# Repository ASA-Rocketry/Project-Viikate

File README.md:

# Project Viikate

## Getting started

```bash
git clone https://github.com/ASA-Rocketry/Project-Viikate
cd Project-Viikate
./setup.sh --wizard --build
```

Run `./setup.sh --help` for options, or see the [codebase setup guide](docs/codebase-setup.md) for prerequisites, manual setup, and flashing instructions.

## Structure

```
project-viikate/
  cad/          -- the fusion files for the structure of the rocket
  code/         -- firmware, simulations and other adjacent software
    firmware/   -- the actual firmware that goes on the rocket
    dashboard/
  docs/         -- textual documentation related to the operations of the project
  minutes/      -- meeting notes
  pcb/          -- electronics, pinouts and the core PCB
```

## Software

## Style Choices

- For details on how to style your code refer to [RocketStyle](./code/README.md).
- For details on how to style your mechanical designs refer to [Mechanical Design Guide for Aalto Space Association Projects with Fusion](./cad/README.md).
- Folder names should follow `kebab-case` unless mandated by the style guide of the specific piece of software.
- Files should follow `snake_case` unless mandated by the style guide of a specific piece of software.

## Testing Policy

The priority of tests is strictly in this order:

0. Structural failures.
1. Serialization/deserialization.
2. Unit conversions.
3. Sensor fusion edgecases.
4. State machine transitions.
5. Numerical stability.
6. Watchdog/fault recovery.

Notice how getters and setters are not included. They are not important.

## How to make Git less painful

- Use rebases instead of merges. Merges pollute history, rebases straighten it back out.
- Don't commit stuff that is not supposed to be `diff`-ed. If you can't meaningfully interpret a file changing across time it should not be in git.
- Don't commit caches. Temporary files, output binaries, stuff like that.
- A commit message should follow the strict `type(scope): Message` format. This is needed to make the scope of the changes easier to understand. For example: `feat(gnc): Add the barrel roll logic`. The accepted types are as follows:
  - `feat` - a new feature, functionality that was previously missing.
  - `fix` - a fix to a bug that was causing trouble.
  - `style` - making some part of the code adhere to a style.
  - `docs` - adding documentation, amending typos.
  - `refactor` - making an old piece of code less ugly.
  - `chore` - reordering files, deleting stuff that shouldn't be tracked, etc.
- The commit text should read as what it does when applied. Not `added more tests`, but `add more tests`.
- Do not include OS-specific files in git. To exclude file locally you can add it to the `.git/info/exclude` file.

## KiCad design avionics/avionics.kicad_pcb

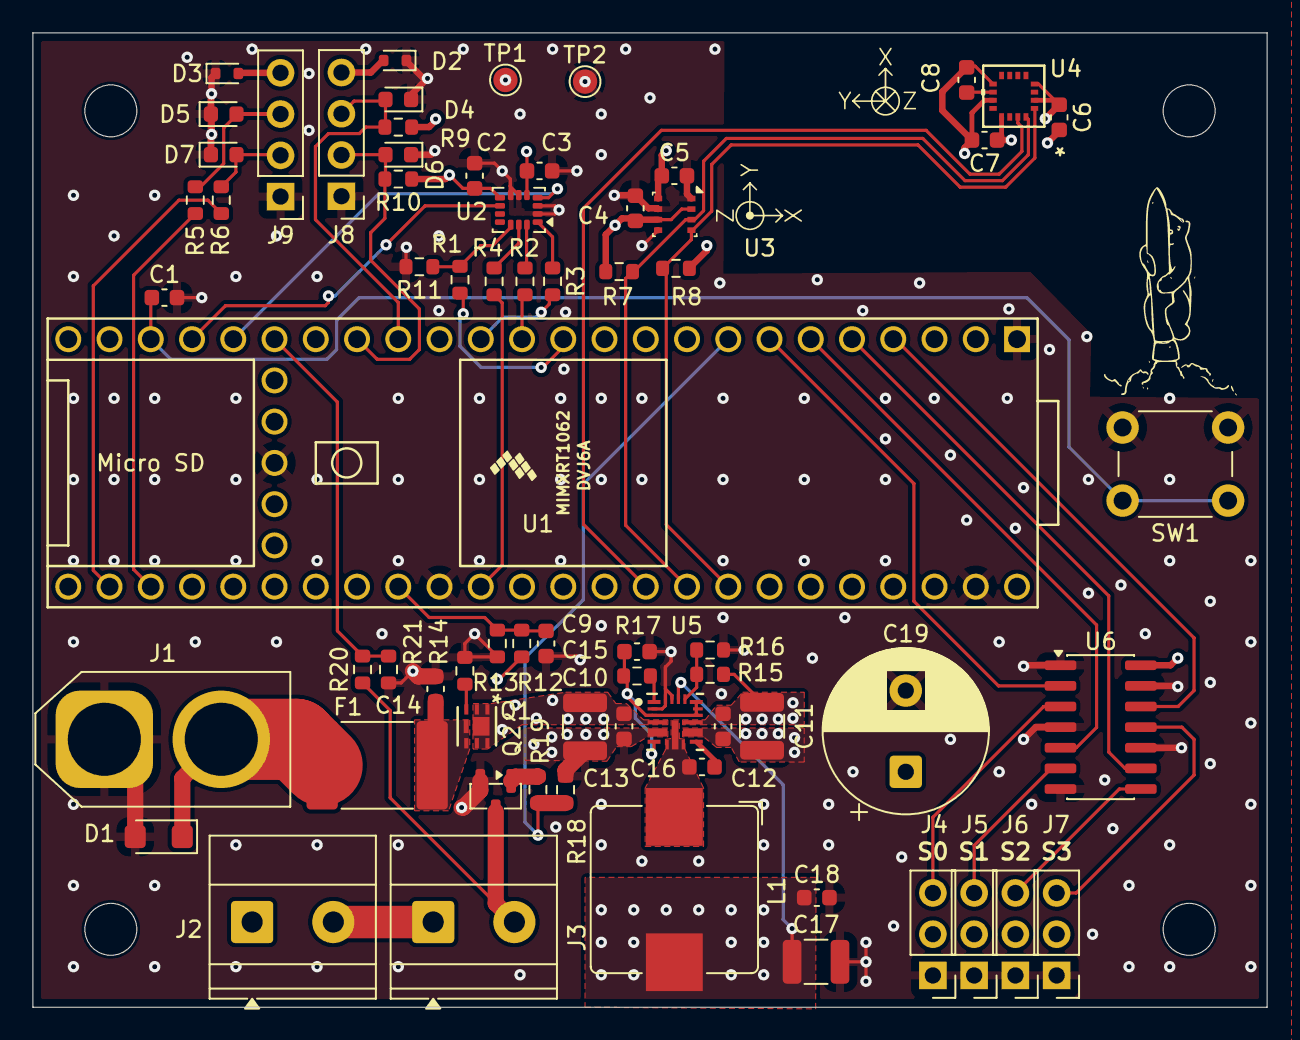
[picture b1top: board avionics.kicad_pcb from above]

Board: 4 copper layers, 76.0 x 60.0 mm, 70 parts (0 on the bottom side), 49 nets.

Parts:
C1, C2, C3, C4, C5, C6, C7, C9, C14, C16: 100n; C_0603_1608Metric
C8: 10u; C_0603_1608Metric
C10, C11: 22u; C_1210_3225Metric
C12, C13, C15, C18: 1u; C_0603_1608Metric
C17: 47u; C_1210_3225Metric
C19: 1000u; CP_Radial_D10.0mm_P5.00mm
D1: SMF10A; D_SMF
D2, D3: CPDH5V0U; D_SOD-523
D4, D5, D6, D7: CPDUR5V0-HF; D_0603_1608Metric
F1: Littelfuse 2920L400; Fuse_2920_7451Metric
J1: XT60M; AMASS_XT60-M_1x02_P7.20mm_Vertical
J2, J3: 1x2_header; TerminalBlock_Phoenix_MKDS-1,5-2_1x02_P5.00mm_Horizontal
J4, J5, J6, J7: 1x3_header; PinHeader_1x03_P2.54mm_Vertical
J8, J9: Conn_01x04_Pin; PinHeader_1x04_P2.54mm_Vertical
L1: 300n; L_Bourns_SRP1038C_10.0x10.0mm
M3: MountingHole_3.2mm_M3
Q1: RF4C050AP; TRANS_RF4C_ROM
Q2: AO3400A; SOT-23
R1, R2, R3, R4, R5, R6, R19: 33; R_0603_1608Metric
R7, R8, R9, R10: 2.7k; R_0603_1608Metric
R11, R18: 100k; R_0603_1608Metric
R12, R20: 56k; R_0603_1608Metric
R13, R21: 33k; R_0603_1608Metric
R14: 47k; R_0603_1608Metric
R15: 37.4k; R_0603_1608Metric
R16, R17: 10k; R_0603_1608Metric
SW1: 6x6mm Switch; SW_PUSH_6mm
TP1: TP_3.3V; TestPoint_Pad_D1.5mm
TP2: TP_GND; TestPoint_Pad_D1.5mm
U1: Teensy4.1; Teensy41
U2: ISM330DHCX; LGA-14_3x2.5mm_P0.5mm_LayoutBorder3x4y
U3: BME280; Bosch_LGA-8_2.5x2.5mm_P0.65mm_ClockwisePinNumbering
U4: MMC5983MA; MMC5983MA_MEM
U5: TPS548B23VANR; VAN0019A-MFG
U6: 74AHCT125; SOIC-14_3.9x8.7mm_P1.27mm

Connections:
+3.3V: C2.1, C3.2, C4.1, C5.1, C6.1, C7.1, R7.1, R8.1, R9.1, R10.1, TP1.1, U1.46 (3V3), U1.51 (3V3), U2.5 (VDDIO), U2.8 (VDD), U3.2 (CSB), U3.6 (VDDIO), U3.8 (VDD), U4.2 (VDD), U4.4 (SPI_CS), U4.13 (VDDIO)
+5V: C17.1, C18.1, C19.1, J4.2, J5.2, J6.2, J7.2, L1.2, U1.48 (VIN), U5.17 (VOS_FB), U6.14 (VCC)
+BATT: C10.1, C11.1, C12.1, C13.1, J2.1, Q1.1, Q1.2, Q1.5, Q1.6, Q1.7, R12.1, R15.1, U5.4 (VIN), U5.12 (VIN)
/BAT_VOLTAGE: C9.1, R12.2, R13.1, U1.33 (41_A17)
/I2C_OUT_SCL: D4.2 (A2), J8.3, R9.2, U1.16 (24_A10_TX6_SCL2)
/I2C_OUT_SDA: D6.2 (A2), J8.2, R10.2, U1.17 (25_A11_RX6_SDA2)
/I2C_SCL: R8.2, U1.41 (19_A5_SCL), U3.4 (SCK), U4.1 (SCL/SPI_SCK)
/I2C_SDA: R7.2, U1.40 (18_A4_SDA), U3.3 (SDI), U4.16 (SDA/SPI_SDI)
/INT_ACC: U1.20 (28_RX7), U2.4 (INT1)
/INT_GYR: U1.21 (29_TX7), U2.9 (INT2)
/Magnetometer/INT: U1.39 (17_A3_TX4_SDA1), U4.15 (INT)
/PSU/BAT_CONN+: D1.1 (A1), F1.1, J1.2
/PYRO_0: R18.1, R19.2, U1.8 (6_OUT1D)
/PYRO_0_CONT: R20.2, R21.1, U1.19 (27_A13_SCK1)
/Pyro_and_servos/ARM_Vout: J2.2, J3.1
/Pyro_and_servos/PYRO_0_GATE: Q2.1 (G), R19.1
/Pyro_and_servos/PYRO_0_Vout: J3.2, Q2.3 (D), R20.1
/Pyro_and_servos/SERVO_0: J4.3, U6.3
/Pyro_and_servos/SERVO_1: J5.3, U6.6
/Pyro_and_servos/SERVO_2: J6.3, U6.8
/Pyro_and_servos/SERVO_3: J7.3, U6.11
/SERVO_0_PWM: U1.7 (5_IN2), U6.2
/SERVO_1_PWM: U1.6 (4_BCLK2), U6.5
/SERVO_2_PWM: U1.5 (3_LRCLK2), U6.9
/SERVO_3_PWM: U1.4 (2_OUT2), U6.12
/SPI_CS: R1.1, R11.1, U2.12 (CS)
/SPI_MISO: R3.1, U2.1 (SDO/SA0)
/SPI_MOSI: R2.1, U2.14 (SDA)
/SPI_SCK: R4.2, U2.13 (SCL)
/SW_GUIDANCE: C1.1, SW1.1, U1.22 (30_CRX3)
/UART_RX: D7.2 (A2), J9.2, R6.2
/UART_TX: D5.2 (A2), J9.3, R5.2
GND: C1.2, C2.2, C3.1, C4.2, C5.2, C6.2, C7.2, C8.1, C9.2, C10.2, C11.2, C12.2, C13.2, C14.2, C15.2, C17.2, C18.2, C19.2, D1.2 (A2), D2.1 (K), D3.1 (K), D4.1 (A1), D5.1 (A1), D6.1 (A1), D7.1 (A1), J1.1, J4.1, J5.1, J6.1, J7.1, J8.1, J9.1, Q2.2 (S), R11.2, R13.2, R14.2, R16.2, R18.2, R21.2, SW1.2, TP2.1, U1.1 (GND), U1.34 (GND), U1.47 (GND), U1.52 (GND), U2.2 (SDx), U2.3 (SCx), U2.6 (GND), U2.7 (GND), U3.1 (GND), U3.5 (SDO), U3.7 (GND), U4.9 (GND), U4.11 (GND), U5.2 (CFG2), U5.5 (PGND), U5.11 (PGND), U5.18 (GOS), U5.19 (AGND), U6.1, U6.4, U6.7 (GND), U6.10, U6.13
unnamed: C14.1, F1.2, Q1.4, Q1.8
unnamed: C16.2, L1.1, U5.7 (SW), U5.8 (SW), U5.9 (SW)
unnamed: D2.2 (A), J8.4
unnamed: D3.2 (A), J9.4
unnamed: Q1.3, R14.1
unnamed: R1.2, U1.12 (10_CS_MQSR)
unnamed: R2.2, U1.13 (11_MOSI_CTX1)
unnamed: R3.2, U1.14 (12_MISO_MQSL)
unnamed: R4.1, U1.35 (13_SCK_LED)
unnamed: R6.1, U1.26 (34_RX8)
unnamed: R5.1, U1.27 (35_TX8)
unnamed: C8.2, U4.10 (CAP)
unnamed: C16.1, U5.10 (BST)
unnamed: C15.1, R17.2, U5.3 (CFG1), U5.6 (VCC), U5.13 (CFG3), U5.14 (CFG4), U5.15 (CFG5)
unnamed: R15.2, R16.1, U5.16 (EN)
unnamed: R17.1, U5.1 (PG)

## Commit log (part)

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2026-03-19 Unified naming
2026-03-22 Added Openrocket V0.4
    Corrected dimensions and weights to match CAD files.
2026-03-24 Changing code to follow Google C++ Style guide with no other changes. https://google.github.io/styleguide/cppguide.html#Naming
2026-03-24 FIle renaming to follow snake case.
2026-03-24 Rename all project files to lowercase snake_case for Google C++ style
2026-03-24 Issues in dependencies.
2026-03-24 toimii pimeällä magialla
2026-03-25 Correctly built files and their renaming.
2026-03-25 fixed an include command
2026-03-25 Rename header and source files to lowercase snake_case
2026-03-25 fixed control.cpp having uppercase name.
2026-03-25 Errorles Version of Flight Code After the Latest Merge.
2026-03-25 Test
2026-03-25 Flight Code now follows GOogle C++ Style Guide, and PlatformIO functions correctly. If you need to ad libraries, do it in the ini file, not the platformIO portal. Always compile the "default" Platfor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
2026-03-25 Update README.md
    Updated schedule flight days
2026-03-25 Made fixes according to the Google standard
2026-03-25 changed a local variable to use the global variable for gravity
2026-03-25 Add files via upload
    Sensor readout testing
2026-03-30 Modified FlightData-Struct to accomodate all sensor axes
2026-03-30 Changed FlightData-struct variable naming convention, fixed all the constant calls to use the new names and fixed a couple of typos
2026-03-31 Added IMU calibration
    Added imucalattempt.ino. This should help calibrate the IMU. Tested and works (kind of), will improve on when I can
2026-04-01 Implemented the PID with antiwindup and control_hardware class
2026-04-01 minimal change to one comment
2026-04-06 Fixed the servo.h-library problem. PIO scans lib_deps first, before any specific board-libraries, so the built in teensy servo-library got overwritten by the uno-library -> incompatibility. Removed u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
2026-04-08 migrating avionics system to platform.io, got working sensor readings and compatibility with gnc's testbench
2026-04-10 Datalogger should no longer cause delays
2026-04-16 adding ekf class (in progress)
2026-04-16 Modified sensors.cpp and main.cpp for exception handling and imu/mag data
    Magnetometer data isn't being saved in FlightData/not being printed. figuring out why
2026-04-16 changed sensors class to call read functions minimally
2026-04-16 Edited such that magnetometer readings can be taken!
    Previously on the serial monitor magnetometer readings were showing up as 0.0, 0.0, 0.0. Problem was due to a float precision issue
2026-04-16 fixed imu buffering issue
2026-04-16 added eigen library (not much here)
2026-04-17 fixed axis on the pcb
2026-04-17 fixed axis issue to make sure all sensor z-axes point "up"
2026-04-17 added ArduinoEigen dependency
2026-04-19 created class structure for kalman filter
2026-04-19 fixed covariance matrix
2026-04-19 Updated sensors.cpp, currently trying to test kalman filter
2026-04-19 initialisation functions fixed
2026-04-19 added new initialisation functions for kalmanfilter
2026-04-19 added observation matrix functionality
2026-04-19 added blank constructors
2026-04-20 Updated to include Kalman filter for accelerometer
    THE KALMAN FILTER WORKS!!! to tweak to account for gravity, will implement for gyroscope as well
2026-04-20 added gyroscope kalman filter, need to fix scaling issues and gravity offsets
2026-04-20 minor bug fixes, current orientation readings are in radians
2026-04-20 fixed servo library build issues
2026-04-20 calibration works
2026-04-20 added tests for control loop
2026-04-20 docs: avionics plan
2026-04-20 docs: setup docs compiler
2026-04-20 testing control loop
2026-04-20 updated sensors to include kalman filter for accX and accY
    Kalman filter has also been implemented for X axis and Y axis acceleration data. Will need to test tomorrow, publishing in a separate branch for now
2026-04-21 Updated PID constants
    Made changes to accelerometer kalman filter matrices and updated PID constants
2026-04-21 Updated PID values and control of D value
    Updated PID values. D value adjusted such that D=0 when error difference is less than 2deg
2026-04-22 Openrocket V0.5
    More accuarate weights and total lenght changed
2026-04-22 testing bluetooth module
2026-04-24 allowing bluetooth connectivity
2026-04-24 random
2026-04-24 json protocol
2026-04-24 we finally got the hc06 to connect
    ignore the python filename please
2026-04-25 fixed conflicts
2026-04-26 visualization progress
2026-04-26 kinda working wind tunnel PID, made tweaks to d-term handling
2026-04-27 PID updates
2026-04-28 WORKS WORKS
2026-04-28 WORKS WORKS ACTUALLY
2026-04-28 Derivative error solved
2026-04-28 Working implementation. Added integrator logic
2026-05-06 Reverted the test environment, and added a simulated_flight_data_1.csv, now we need to implement precompile flags, to run the statemachine with fake data.
2026-05-07 Added a "calibration and PID test" environment, which is equal to our previous pid simulations, and production flight mode. still debugging sd card reading
2026-05-08 Enviroments work now, and each initialization returns and prints.
2026-05-08 Added accessors and integrated the state machine into TEST_STATE_MACHINE mode. Initialization checks still need to be implemented in the Sensors module, following the same pattern as DataLogger, to e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
2026-05-11 The preprocessor directives are now not duplicated.
2026-05-11 Implemented final initialization checks for the Calibration state, fixed spelling mistakes, ect.
2026-05-11 Small changes.
2026-05-11 Slight changes to latching logic.
2026-05-11 Slight I Identity change, all modes fail with an Eigen error.
2026-05-11 reverted pose changes.
2026-05-11 All code files updated with a space at the beginning.
2026-05-11 Revert branch back to 3f910d0 working state
2026-05-11 Added initialisation checks for control class.
2026-05-12 Simplified the setup in Main.cpp and the servo naming. Both have been tested and work.
2026-05-12 Main refactoring done, uploads work.
2026-05-12 Added a delay for the simulated data.
2026-05-12 Fixed the servo offset.
2026-05-12 rbfPin now works. Added control into idle guard.
2026-05-13 Reduced spaghetti everywhere
2026-05-19 Expanded debug prints, by making it a header, and including it everywhere. Also added a "non functioning" check to sensors for future implementation.
2026-05-21 Returned ternary operators for roll maneuver.
2026-05-23 Further spaghetti reduction and other refinements
2026-05-25 Added EDR template
2026-05-25 Simpler Design Decision Record (DDR) established
2026-05-25 Rename design_decision_record_template to design_decision_record_template.md
2026-05-25 Update README with decision tracking information
    Added note about marking decisions in team folders.
2026-05-25 Added DDR to avionics
2026-05-25 Update avionics DDR format and section headings
2026-05-25 Create design decision record template
2026-05-26 Update README with kickoff meeting notes
    Expanded project instructions relating to documentation for phase 1.2, workflow adjustments, and next steps.
2026-05-26 Wipe everything
2026-05-26 init: Initial commit for v1.1
2026-05-26 docs: Fix a typo
2026-05-27 feat: Compile the binary for the host with the new HAL
2026-05-27 fix: Correctly compile host binary with meson
2026-05-27 fix: Temporarily exclude the firmware/include folder while it's empty
2026-05-27 feat: Run the executable for 1 second in CI/CD
2026-05-27 feat(build): add nix flake for devshell
2026-05-27 feat(build): add linmath.h to shared include
2026-05-27 style: adjust .clang-format from Google style to Rust-like style
2026-05-27 style: Adhere to the style
2026-05-27 feat: Make the precommit hook run always
2026-05-28 feat: Add more typedefs for primitive types
2026-05-28 feat: Add static vector
2026-05-28 fix: Update repository URL in README.md
2026-05-28 fix: Fix the link in the README
2026-05-28 feat: Add a very raw HAL for the Teensy 4.1
2026-06-01 docs(RFC): Viikate avionics v2 first draft
